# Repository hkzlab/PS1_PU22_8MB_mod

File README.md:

# PlayStation PU-22 8MB RAM Daughterboard

## DISCLAIMER

Any use of this project is **under your own responsibility**.
You will be responsible of checking the correct construction and functionality of your board.
By using this project You will agree that I cannot be held responsible if it will destroy any of your devices, damage your computer, burn down your house or whatever.

## Introduction

This daughter board replaces the single main RAM IC on your PU-22 motherboard with 4 2Mx8 ICs, shuffles some address lines and provides your PlayStation with 8MB of addressable memory.

I tested this on my european SCPH-7502 console, with a PU-22 motherboard in it. The board boots fine and all the 8MB are addressable.
It could work on other models too, but as of now, this is the only tested one.

### Support

If you wish to support me in building new hardware and software for old machines, [throw a few euros in my direction via Ko-Fi](https://ko-fi.com/hkzlab) ☕!

### 💰 Selling these boards 💰

I you want to contact me about selling this project, you can reach me via email at `0hkzUNDERSCOREprojects6ATposteoDOTnet` after properly fixing the email address by removing the digits and replacing the uppercase words with the proper characters.

**Contacts via other channels will be ignored**, as it means you did not read this document thoroughly.

"Collaborations" will boil down to the following:

- If you wish to produce and share this project at a loss or at cost, go for it. I am only asking for attribution and to let me know via email.
- If you want to do it for profit, let's discuss it. I'll probably settle for a rough 5% of the profit. Importing components is getting more expensive by the day, so this will contribute to me making future projects available for free.
- I will NOT do customer assistance for you or your customers. This is a hobby, not my job.

If this is not ok for you, you're cordially invited to go bother someone else :)

Authorized sellers will be listed in this README. If you find someone selling my boards without being listed here, it means they're stealing other people's work.

## Hardware

The board was designed with [KiCad](https://kicad.org/) EDA.

The board **MUST** be produced on a flexible PCB!

### Installation instructions

Disassemble your PlayStation, extract the motherboard and make sure the model is a PU-22.

⚠️WARNING⚠️: This mod probably works on all units with this type of RAM and processor, but it has been tested on PU-22 units only, as of now.

Assemble the daughterboard, soldering caps and memory ICs.

Desolder the inner shield covering the main ICs, including the RAM.

Cover the components around RAM "IC106" with kapton tape, to protect them during desoldering.

Desolder the RAM IC using hot air, then clean the pads using flux and solder wick.

Solder the board to the old RAM pads, make sure to solder the board in the correct orientation. Pin one has a tiny arrow printed on it, match it on pin 1 on the motherboard.

You now need to solder two wires to the CPU, to extract A10 and A8. A10 is pin 56, A8 is pin 58.

You can then solder these lines to the pads with matching names on the daughterboard.

You can now reinstall the shield, but before inserting it, bend inward the part of the shield that went through the PCB near the RAM pad, make it almost flush to the shield, so it doesn't block the way for the daughterboard to get out.

Once reinstalled, cover the part of the shield where the daughterboard will sit with tape, so there is no chance of shorting.

Solder the daughterboard GND pad to the shield, use rigid wire so it keeps the daughterboard in place.

You can put tape over the daughterboard too, to avoid shorting, then reassemble the unit.

### Bill of Materials

| Component         | Qty | Type / Value                   | Notes                                                    |
| ----------------- | --- | ------------------------------ | -------------------------------------------------------- |
| C1 - C4           |  4  | 100nF / 1206 / ceramic         |                                                          |
| U1 - U4           |  4  | KM48V2104ALT-6                 | Compatible memory can be used                            |

### Ordering the boards

You can order the board for this project at [PCBWay](https://www.pcbway.com/project/shareproject/PlayStation_PU_22_8MB_RAM_Daughterboard_6c497b7f.html) and support me or download 
the gerbers and have them printed wherever you like!!!

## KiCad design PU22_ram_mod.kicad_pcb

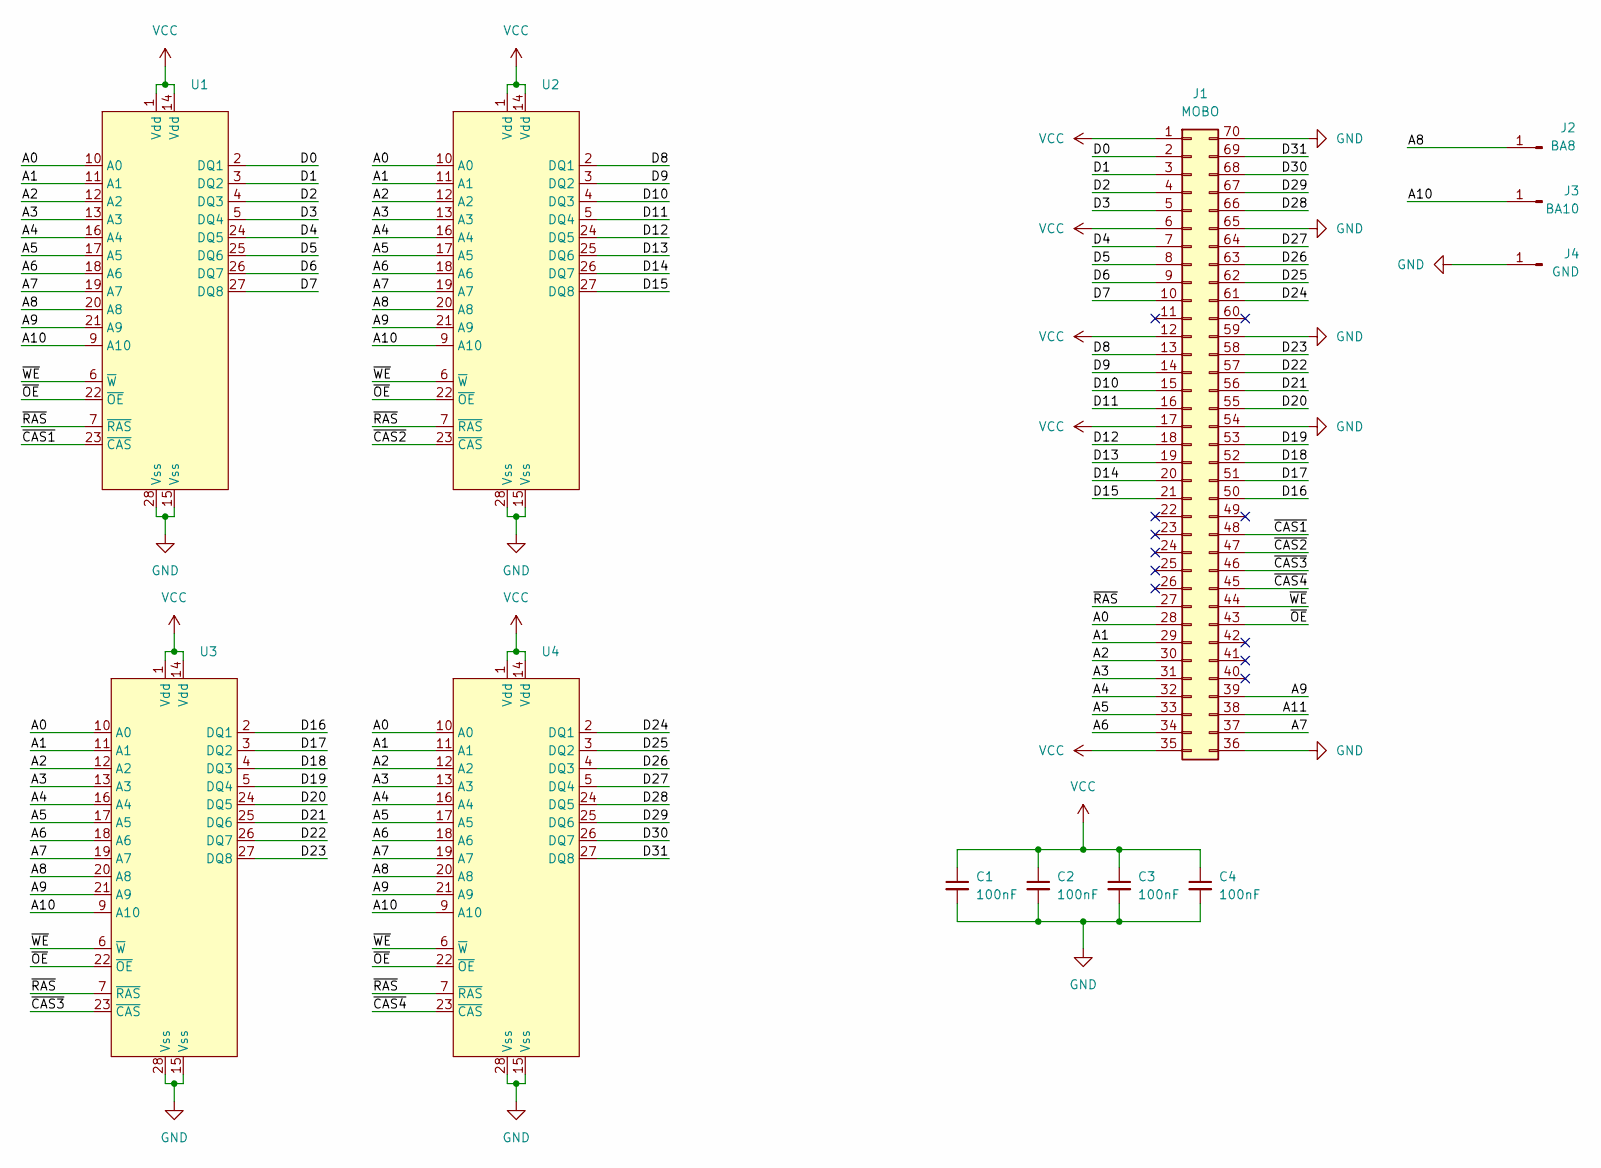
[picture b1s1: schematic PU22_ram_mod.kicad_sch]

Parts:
C1, C2, C3, C4: 100nF; C_1206_3216Metric_Pad1.33x1.80mm_HandSolder
J1: MOBO; SOJ70_castellated
J2: BA8; TestPoint_Pad_D2.5mm
J3: BA10; TestPoint_Pad_D2.5mm
J4: GND; TestPoint_Pad_D2.5mm
U1, U2, U3, U4: SOP-28_DRAM

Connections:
/A0: J1.28, U1.10 (A0), U2.10 (A0), U3.10 (A0), U4.10 (A0)
/A1: J1.29, U1.11 (A1), U2.11 (A1), U3.11 (A1), U4.11 (A1)
/A2: J1.30, U1.12 (A2), U2.12 (A2), U3.12 (A2), U4.12 (A2)
/A3: J1.31, U1.13 (A3), U2.13 (A3), U3.13 (A3), U4.13 (A3)
/A4: J1.32, U1.16 (A4), U2.16 (A4), U3.16 (A4), U4.16 (A4)
/A5: J1.33, U1.17 (A5), U2.17 (A5), U3.17 (A5), U4.17 (A5)
/A6: J1.34, U1.18 (A6), U2.18 (A6), U3.18 (A6), U4.18 (A6)
/A7: J1.37, U1.19 (A7), U2.19 (A7), U3.19 (A7), U4.19 (A7)
/A8: J2.1, U1.20 (A8), U2.20 (A8), U3.20 (A8), U4.20 (A8)
/A9: J1.39, U1.21 (A9), U2.21 (A9), U3.21 (A9), U4.21 (A9)
/A10: J3.1, U1.9 (A10), U2.9 (A10), U3.9 (A10), U4.9 (A10)
/A11: J1.38
/D0: J1.2, U1.2 (DQ1)
/D1: J1.3, U1.3 (DQ2)
/D2: J1.4, U1.4 (DQ3)
/D3: J1.5, U1.5 (DQ4)
/D4: J1.7, U1.24 (DQ5)
/D5: J1.8, U1.25 (DQ6)
/D6: J1.9, U1.26 (DQ7)
/D7: J1.10, U1.27 (DQ8)
/D8: J1.13, U2.2 (DQ1)
/D9: J1.14, U2.3 (DQ2)
/D10: J1.15, U2.4 (DQ3)
/D11: J1.16, U2.5 (DQ4)
/D12: J1.18, U2.24 (DQ5)
/D13: J1.19, U2.25 (DQ6)
/D14: J1.20, U2.26 (DQ7)
/D15: J1.21, U2.27 (DQ8)
/D16: J1.50, U3.2 (DQ1)
/D17: J1.51, U3.3 (DQ2)
/D18: J1.52, U3.4 (DQ3)
/D19: J1.53, U3.5 (DQ4)
/D20: J1.55, U3.24 (DQ5)
/D21: J1.56, U3.25 (DQ6)
/D22: J1.57, U3.26 (DQ7)
/D23: J1.58, U3.27 (DQ8)
/D24: J1.61, U4.2 (DQ1)
/D25: J1.62, U4.3 (DQ2)
/D26: J1.63, U4.4 (DQ3)
/D27: J1.64, U4.5 (DQ4)
/D28: J1.66, U4.24 (DQ5)
/D29: J1.67, U4.25 (DQ6)
/D30: J1.68, U4.26 (DQ7)
/D31: J1.69, U4.27 (DQ8)
/~CAS1: J1.48, U1.23 (~CAS)
/~CAS2: J1.47, U2.23 (~CAS)
/~CAS3: J1.46, U3.23 (~CAS)
/~CAS4: J1.45, U4.23 (~CAS)
/~OE: J1.43, U1.22 (~OE), U2.22 (~OE), U3.22 (~OE), U4.22 (~OE)
/~RAS: J1.27, U1.7 (~RAS), U2.7 (~RAS), U3.7 (~RAS), U4.7 (~RAS)
/~WE: J1.44, U1.6 (~W), U2.6 (~W), U3.6 (~W), U4.6 (~W)
GND: C1.2, C2.2, C3.2, C4.2, J1.36, J1.54, J1.59, J1.65, J1.70, J4.1, U1.15 (Vss), U1.28 (Vss), U2.15 (Vss), U2.28 (Vss), U3.15 (Vss), U3.28 (Vss), U4.15 (Vss), U4.28 (Vss)
VCC: C1.1, C2.1, C3.1, C4.1, J1.1, J1.6, J1.12, J1.17, J1.35, U1.1 (Vdd), U1.14 (Vdd), U2.1 (Vdd), U2.14 (Vdd), U3.1 (Vdd), U3.14 (Vdd), U4.1 (Vdd), U4.14 (Vdd)

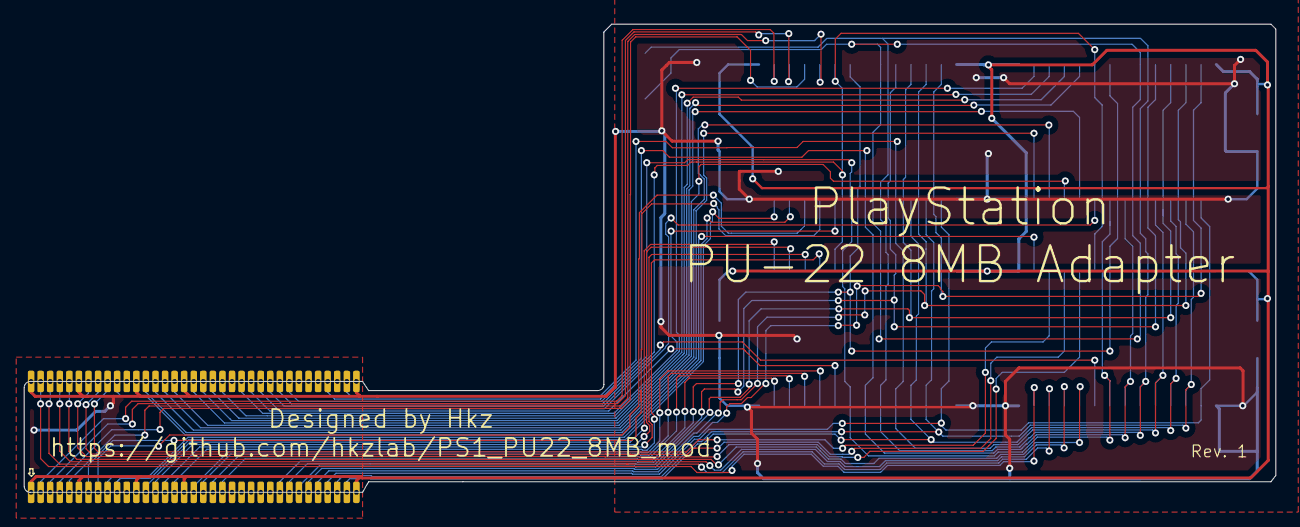
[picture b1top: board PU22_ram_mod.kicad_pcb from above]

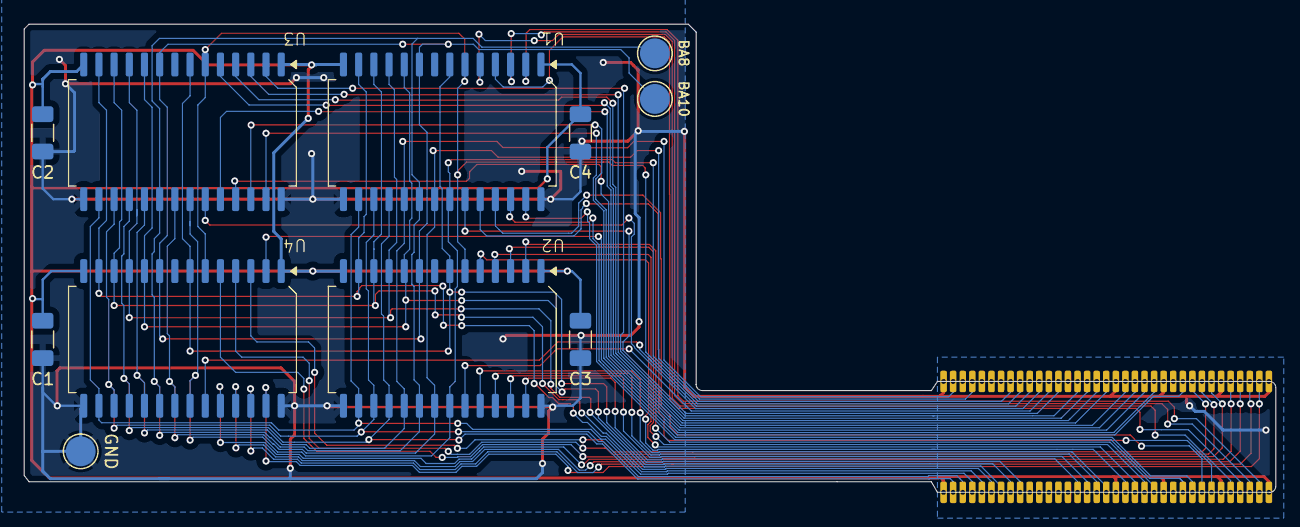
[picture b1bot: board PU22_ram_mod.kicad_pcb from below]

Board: 2 copper layers, 104.6 x 39.1 mm, 12 parts (11 on the bottom side), 52 nets.

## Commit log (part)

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2024-07-30 Add basic needed footprints
2024-07-30 Begin drawing the schematic to expand the memory
2024-07-31 Update schematic
2024-07-31 Some tracing
2024-07-31 some more organizing
2024-08-01 Some routing
2024-08-01 Routing
2024-08-01 Update traces
2024-08-01 Tweaked traces a bit
2024-08-02 make PCB a bit longer
2024-08-02 Change outline
2024-08-06 Reroute traces
2024-08-06 More routing
2024-08-06 Add copper fill in the zone with RAMs
2024-08-06 Some more ground plane
2024-08-07 Update the routing of some traces to increase distance from pads
2024-08-07 Readd refill
2024-08-07 more fixes
2024-08-07 Refill
2024-08-07 Added silkscreen
2024-08-07 Add some gnd filling in soldered connector too
2024-08-21 Add schematics and readme
2024-08-22 Fix readme header
2024-08-22 Update silkscreen, begin writing small tutorial
2024-08-22 Added pics and remaining instructions
2024-08-22 Renamed file
2024-08-22 Upload datasheets
2024-08-22 Additional README details
2024-08-22 Further README updates
2025-09-07 Update the README mentioning producing on PCBWay
